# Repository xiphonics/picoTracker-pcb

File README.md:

# PCB for PicoTracker
All data in order to fabricate the PCB for the [picoTracker](https://github.com/xiphonics/picoTracker)

Buy the official kit at [xiphonics store](https://xiphonics.com/products/picotracker-pcb-kit)
# Trademark Notice

This repository contains the open-source hardware design files for the picoTracker project.

The hardware design files are released under the CC0 1.0 Universal license and may be used, modified, manufactured, and sold without restriction.

However, the **picoTracker** name, logos, product branding, and associated trademarks are **not** covered by the CC0 license and are not licensed for use by third parties.

You may manufacture and sell hardware derived from these design files, but you may not market, advertise, label, or otherwise represent such products using the "picoTracker" name or branding without prior written permission from Xiphonics.

Products manufactured from these files must be sold under a different product name and must not imply endorsement by, affiliation with, or origin from Xiphonics.

To facilitate this separation, the manufacturing files distributed through this repository intentionally omit picoTracker branding elements.

Use of the picoTracker name in connection with unauthorized derivative hardware may constitute trademark infringement and unfair competition.

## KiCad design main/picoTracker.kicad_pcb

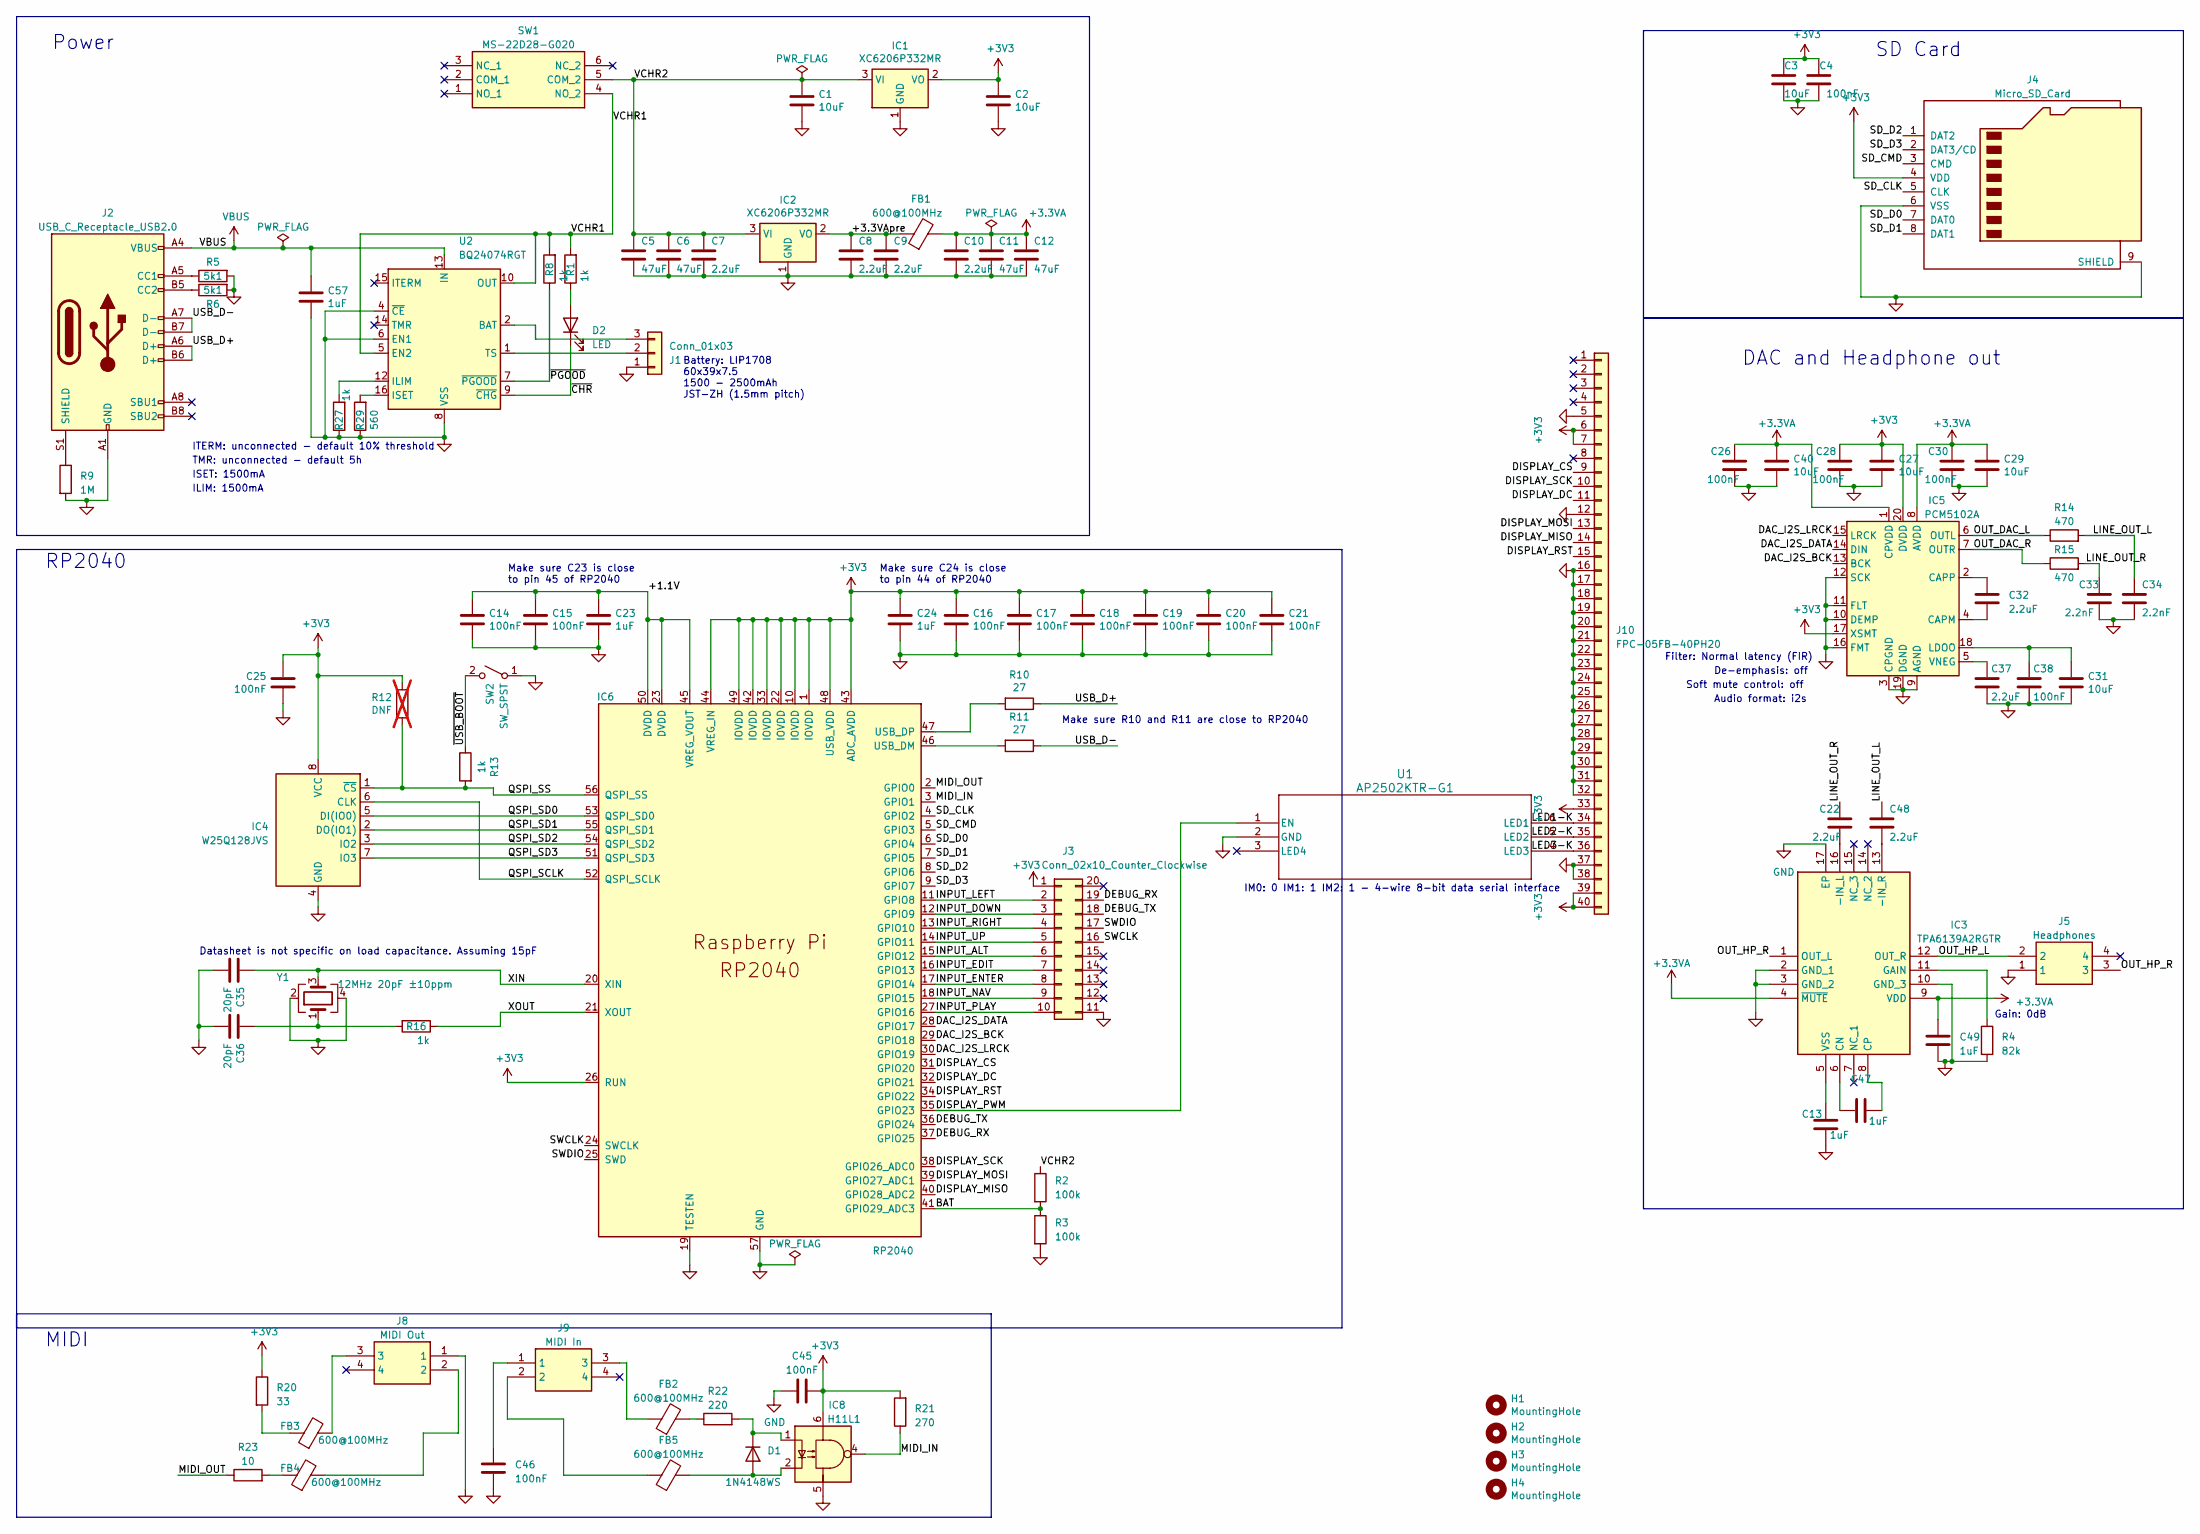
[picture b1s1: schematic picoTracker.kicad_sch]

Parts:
C1, C2, C3, C27, C29, C31, C40: 10uF; C_0603_1608Metric; LCSC C19702
C4, C14, C15, C16, C17, C18, C19, C20, C21, C25, C26, C28, C30, C38, C45, C46: 100nF; C_0603_1608Metric; LCSC C14663
C5, C6, C11, C12: 47uF; C_0805_2012Metric; LCSC C16780
C7, C8, C9, C10, C22, C32, C37, C48: 2.2uF; C_0603_1608Metric; LCSC C23630
C13, C23, C24, C47, C49, C57: 1uF; C_0603_1608Metric; LCSC C15849
C33, C34: 2.2nF; C_0603_1608Metric; LCSC C1604
C35, C36: 20pF; C_0603_1608Metric; LCSC C1648
D1: 1N4148WS; D_SOD-323; LCSC C2128
D2: LED; LED_0603_1608Metric; LCSC C2286
FB1, FB2, FB3, FB4, FB5: 600@100MHz; R_0805_2012Metric; LCSC C1017
H1, H2, H3, H4: MountingHole; MountingHole_3.2mm_M3
IC1, IC2: XC6206P332MR; SOT-23; LCSC C5446
IC3: TPA6139A2RGTR; QFN50P300X300X100-17N-D; Mouser Part Number 595-TPA6139A2RGTR
IC4: W25Q128JVS; SOIC-8_5.23x5.23mm_P1.27mm; LCSC C97521
IC5: PCM5102A; TSSOP-20_4.4x6.5mm_P0.65mm; LCSC C107671
IC6: RP2040; QFN-56-1EP_7x7mm_P0.4mm_EP3.2x3.2mm; LCSC C2040
IC8: H11L1; SMDIP-6_W9.53mm; LCSC C78589
J1: Conn_01x03; CONN_S3B-ZR-SM4A-TFLFSN_JST; LCSC C72591
J2: USB_C_Receptacle_USB2.0; USB_C_Receptacle_G-Switch_GT-USB-7010ASV; LCSC C2988369
J3: Conn_02x10_Counter_Clockwise; Hirose_DF12_DF12C3.0-20DS-0.5V_2x10_P0.50mm_Vertical; LCSC C3645324
J4: Micro_SD_Card; Xunpu_TF-115_microSD; LCSC C720505
J5: Headphones; PJ327C4A; Manufacturer_Part_Number PJ-327C-4A; LCSC C145813
J8: MIDI Out; PJ327C4A; Manufacturer_Part_Number PJ-327C-4A; LCSC C145813
J9: MIDI In; PJ327C4A; Manufacturer_Part_Number PJ-327C-4A; LCSC C145813
J10: FPC-05FB-40PH20; FPC_40-flap; LCSC C2856837
R1, R8, R13, R16, R27: 1k; R_0603_1608Metric; LCSC C21190
R2, R3: 100k; R_0603_1608Metric; LCSC C25803
R4: 82k; R_0805_2012Metric; LCSC C17840
R5, R6: 5k1; R_0603_1608Metric; LCSC C23186
R9: 1M; R_0603_1608Metric; LCSC C22935
R10, R11: 27; R_0603_1608Metric; LCSC C25190
R12: DNF; R_0603_1608Metric; not fitted
R14, R15: 470; R_0603_1608Metric; LCSC C23179
R20: 33; R_0603_1608Metric; LCSC C23140
R21: 270; R_0603_1608Metric; LCSC C22966
R22: 220; R_0402_1005Metric; LCSC C1111
R23: 10; R_0603_1608Metric; LCSC C22859
R29: 560; R_0603_1608Metric; LCSC C23204
SW1: MS-22D28-G020; MS22D28G020; Manufacturer_Part_Number MS-22D28-G020; LCSC C963205
SW2: SW_SPST; SW_Push_1P1T_XKB_TS-1187A; LCSC C318884
U1: AP2502KTR-G1; SOT23-6_DIO; LCSC C460349
U2: BQ24074RGT; VQFN-16-1EP_3x3mm_P0.5mm_EP1.6x1.6mm; LCSC C54313
Y1: 12MHz 20pF ±10ppm; Crystal_SMD_3225-4Pin_3.2x2.5mm; LCSC C9002

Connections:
+3.3VA: C10.1, C11.1, C12.1, C26.1, C29.1, C30.1, C40.1, C49.1, FB1.2, IC3.4 (~MUTE), IC3.9 (VDD), IC5.1 (CPVDD), IC5.8 (AVDD)
+3V3: C2.1, C3.1, C4.1, C16.1, C17.1, C18.1, C19.1, C20.1, C21.1, C24.1, C25.1, C27.1, C28.1, C45.2, IC1.2 (VO), IC4.8 (VCC), IC5.17 (XSMT), IC5.20 (DVDD), IC6.1 (IOVDD), IC6.10 (IOVDD), IC6.22 (IOVDD), IC6.26 (RUN), IC6.33 (IOVDD), IC6.42 (IOVDD), IC6.43 (ADC_AVDD), IC6.44 (VREG_IN), IC6.48 (USB_VDD), IC6.49 (IOVDD), IC8.6, J3.1, J4.4 (VDD), J10.6, J10.7, J10.33, J10.39, J10.40, R12.1, R20.1, R21.2
/+1.1V: C14.1, C15.1, C23.1, IC6.23 (DVDD), IC6.45 (VREG_VOUT), IC6.50 (DVDD)
/+3.3VApre: C8.1, C9.1, FB1.1, IC2.2 (VO)
/BAT: IC6.41 (GPIO29_ADC3), R2.2, R3.1
/DAC_I2S_BCK: IC5.13 (BCK), IC6.29 (GPIO18)
/DAC_I2S_DATA: IC5.14 (DIN), IC6.28 (GPIO17)
/DAC_I2S_LRCK: IC5.15 (LRCK), IC6.30 (GPIO19)
/DEBUG_RX: IC6.37 (GPIO25), J3.19
/DEBUG_TX: IC6.36 (GPIO24), J3.18
/DISPLAY_CS: IC6.31 (GPIO20), J10.9
/DISPLAY_DC: IC6.32 (GPIO21), J10.11
/DISPLAY_MISO: IC6.40 (GPIO28_ADC2), J10.14
/DISPLAY_MOSI: IC6.39 (GPIO27_ADC1), J10.13
/DISPLAY_PWM: IC6.35 (GPIO23), U1.1 (EN)
/DISPLAY_RST: IC6.34 (GPIO22), J10.15
/DISPLAY_SCK: IC6.38 (GPIO26_ADC0), J10.10
/INPUT_ALT: IC6.15 (GPIO12), J3.6
/INPUT_DOWN: IC6.12 (GPIO9), J3.3
/INPUT_EDIT: IC6.16 (GPIO13), J3.7
/INPUT_ENTER: IC6.17 (GPIO14), J3.8
/INPUT_LEFT: IC6.11 (GPIO8), J3.2
/INPUT_NAV: IC6.18 (GPIO15), J3.9
/INPUT_PLAY: IC6.27 (GPIO16), J3.10
/INPUT_RIGHT: IC6.13 (GPIO10), J3.4
/INPUT_UP: IC6.14 (GPIO11), J3.5
/LED1-K: J10.34, U1.6 (LED1)
/LED2-K: J10.35, U1.5 (LED2)
/LED3-K: J10.36, U1.4 (LED3)
/LINE_OUT_L: C34.1, C48.1, R14.2
/LINE_OUT_R: C22.1, C33.1, R15.2
/MIDI_IN: IC6.3 (GPIO1), IC8.4, R21.1
/MIDI_OUT: IC6.2 (GPIO0), R23.1
/OUT_DAC_L: IC5.6 (OUTL), R14.1
/OUT_DAC_R: IC5.7 (OUTR), R15.1
/OUT_HP_L: IC3.12 (OUT_R), J5.2
/OUT_HP_R: IC3.1 (OUT_L), J5.3
/QSPI_SCLK: IC4.6 (CLK), IC6.52 (QSPI_SCLK)
/QSPI_SD0: IC4.5 (DI(IO0)), IC6.53 (QSPI_SD0)
/QSPI_SD1: IC4.2 (DO(IO1)), IC6.55 (QSPI_SD1)
/QSPI_SD2: IC4.3 (IO2), IC6.54 (QSPI_SD2)
/QSPI_SD3: IC4.7 (IO3), IC6.51 (QSPI_SD3)
/QSPI_SS: IC4.1 (~CS), IC6.56 (QSPI_SS), R12.2, R13.2
/SD_CLK: IC6.4 (GPIO2), J4.5 (CLK)
/SD_CMD: IC6.5 (GPIO3), J4.3 (CMD)
/SD_D0: IC6.6 (GPIO4), J4.7 (DAT0)
/SD_D1: IC6.7 (GPIO5), J4.8 (DAT1)
/SD_D2: IC6.8 (GPIO6), J4.1 (DAT2)
/SD_D3: IC6.9 (GPIO7), J4.2 (DAT3/CD)
/SWCLK: IC6.24 (SWCLK), J3.16
/SWDIO: IC6.25 (SWD), J3.17
/USB_D+: J2.A6 (D+), J2.B6 (D+), R10.1
/USB_D-: J2.A7 (D-), J2.B7 (D-), R11.1
/VCHR1: R1.2, R8.2, SW1.4 (NO_2), U2.5 (EN2), U2.10 (OUT), U2.11 (OUT)
/VCHR2: C1.1, C5.1, C6.1, C7.1, IC1.3 (VI), IC2.3 (VI), R2.1, SW1.5 (COM_2)
/XIN: C35.1, IC6.20 (XIN), Y1.3
/XOUT: IC6.21 (XOUT), R16.1
/~CHR: D2.1 (K), U2.9 (~CHG)
/~PGOOD: R8.1, U2.7 (~PGOOD)
/~USB_BOOT: R13.1, SW2.2 (B)
GND: C1.2, C2.2, C3.2, C4.2, C5.2, C6.2, C7.2, C8.2, C9.2, C10.2, C11.2, C12.2, C13.2, C14.2, C15.2, C16.2, C17.2, C18.2, C19.2, C20.2, C21.2, C23.2, C24.2, C25.2, C26.2, C27.2, C28.2, C29.2, C30.2, C31.2, C33.2, C34.2, C35.2, C36.2, C37.2, C38.2, C40.2, C45.1, C46.2, C49.2, C57.2, IC1.1 (GND), IC2.1 (GND), IC3.2 (GND_1), IC3.3 (GND_2), IC3.10 (GND_3), IC3.17 (EP), IC4.4 (GND), IC5.3 (CPGND), IC5.9 (AGND), IC5.10 (DEMP), IC5.11 (FLT), IC5.12 (SCK), IC5.16 (FMT), IC5.19 (DGND), IC6.19 (TESTEN), IC6.57 (GND), IC8.5, J1.1, J2.A1 (GND), J2.A12 (GND), J2.B1 (GND), J2.B12 (GND), J3.11, J4.6 (VSS), J4.9 (SHIELD), J5.1, J8.1, J10.5, J10.12, J10.16, J10.17, J10.18, J10.19, J10.20, J10.21, J10.22, J10.23, J10.24, J10.25, J10.26, J10.27, J10.28, J10.29, J10.30, J10.31, J10.32, J10.37, J10.38, R3.2, R4.2, R5.2, R6.2, R9.2, R27.1, R29.1, SW2.1 (A), U1.2 (GND), U2.4 (~CE), U2.6 (EN1), U2.8 (VSS), U2.17 (VSS), Y1.2, Y1.4
unnamed: C36.1, R16.2, Y1.1
unnamed: C46.1, J9.1
unnamed: D1.2 (A), FB5.2, IC8.2
unnamed: D1.1 (K), IC8.1, R22.2
unnamed: D2.2 (A), R1.1
unnamed: FB2.1, J9.3
unnamed: FB2.2, R22.1
unnamed: FB3.1, R20.2
unnamed: FB3.2, J8.3
unnamed: FB4.1, R23.2
unnamed: FB4.2, J8.2
unnamed: FB5.1, J9.2
unnamed: C22.2, IC3.16 (-IN_L)
unnamed: C48.2, IC3.13 (-IN_R)
unnamed: C47.1, IC3.6 (CN)
unnamed: C47.2, IC3.8 (CP)
unnamed: IC3.11 (GAIN), R4.1
unnamed: C13.1, IC3.5 (VSS)
unnamed: C32.2, IC5.4 (CAPM)
unnamed: C32.1, IC5.2 (CAPP)
unnamed: C31.1, C38.1, IC5.18 (LDOO)
unnamed: C37.1, IC5.5 (VNEG)
unnamed: IC6.46 (USB_DM), R11.2
unnamed: IC6.47 (USB_DP), R10.2
unnamed: J1.2, U2.1 (TS)
unnamed: J1.3, U2.2 (BAT), U2.3 (BAT)
unnamed: J2.A5 (CC1), R5.1
unnamed: J2.B5 (CC2), R6.1
unnamed: J2.S1 (SHIELD), R9.1
unnamed: R27.2, U2.12 (ILIM)
unnamed: R29.2, U2.16 (ISET)
VBUS: C57.1, J2.A4 (VBUS), J2.A9 (VBUS), J2.B4 (VBUS), J2.B9 (VBUS), U2.13 (IN)

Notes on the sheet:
DAC and Headphone out
Gain: 0dB
ITERM: unconnected - default 10% threshold
SD Card
Battery: LIP1708 60x39x7.5 1500 - 2500mAh JST-ZH (1.5mm pitch)
Power
RP2040
Filter: Normal latency (FIR)
IM0: 0 IM1: 1 IM2: 1 - 4-wire 8-bit data serial interface
Datasheet is not specific on load capacitance. Assuming 15pF
ILIM: 1500mA
ISET: 1500mA
TMR: unconnected - default 5h
Make sure C23 is close to pin 45 of RP2040
Soft mute control: off
Make sure R10 and R11 are close to RP2040
De-emphasis: off
MIDI
Audio format: i2s
Make sure C24 is close to pin 44 of RP2040

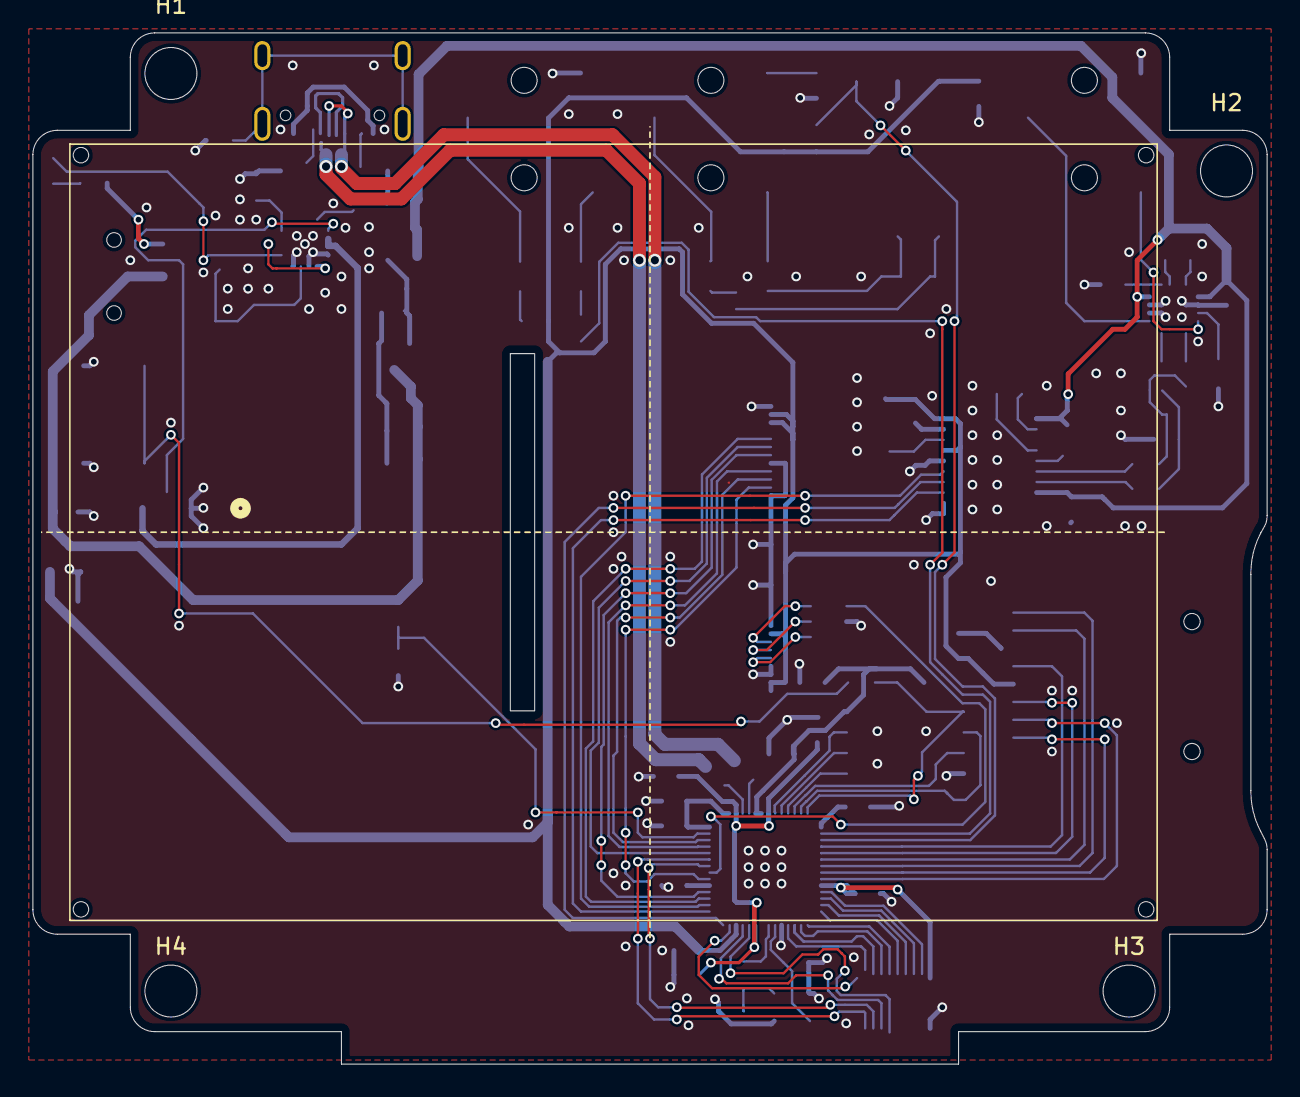
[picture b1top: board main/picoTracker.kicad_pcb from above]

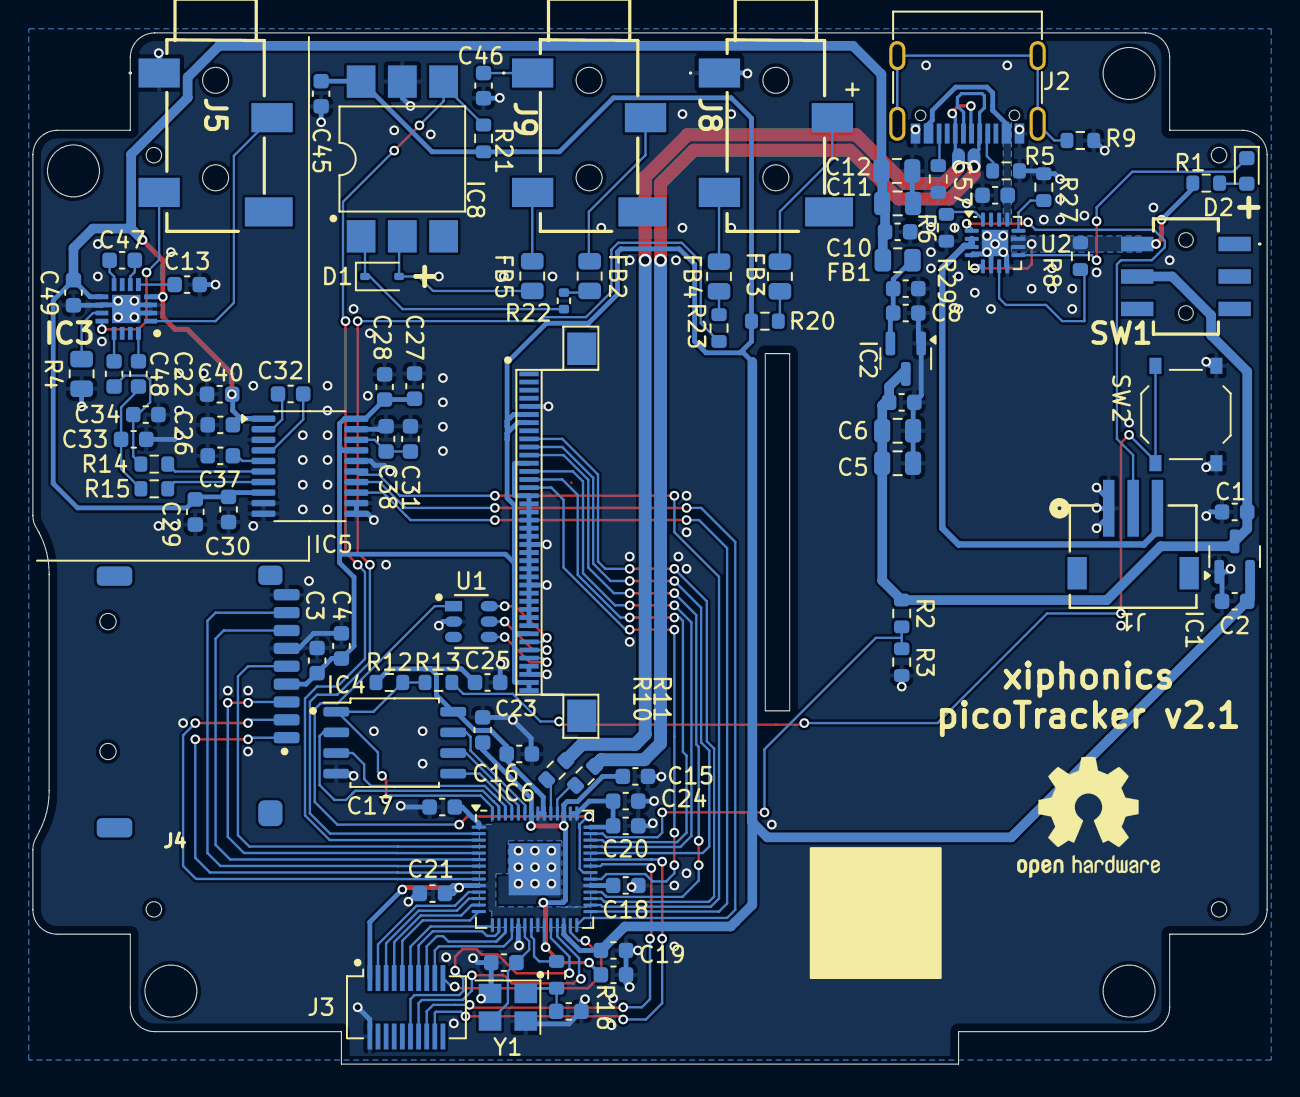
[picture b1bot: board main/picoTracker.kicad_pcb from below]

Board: 2 copper layers, 76.0 x 63.5 mm, 97 parts (93 on the bottom side), 93 nets.

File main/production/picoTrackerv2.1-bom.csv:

Designator,Footprint,Quantity,Value,LCSC Part #
"C1, C2, C27, C29, C3, C31, C40",0603,7,10uF,C19702
"C10, C22, C32, C37, C48, C7, C8, C9",0603,8,2.2uF,C23630
"C11, C12, C5, C6",0805,4,47uF,C16780
"C13, C23, C24, C47, C49, C57",0603,6,1uF,C15849
"C14, C15, C16, C17, C18, C19, C20, C21, C25, C26, C28, C30, C38, C4, C45, C46",0603,16,100nF,C14663
"C33, C34",0603,2,2.2nF,C1604
"C35, C36",0603,2,20pF,C1648
D1,D_SOD-323,1,1N4148WS,C2128
D2,0603,1,LED,C2286
"FB1, FB2, FB3, FB4, FB5",0805,5,600@100MHz,C1017
"H1, H2, H3, H4",MountingHole_3.2mm_M3,4,MountingHole,
"IC1, IC2",SOT-23,2,XC6206P332MR,C5446
IC3,QFN50P300X300X100-17N-D,1,TPA6139A2RGTR,C2868391
IC4,SOIC-8_5.23x5.23mm_P1.27mm,1,W25Q128JVS,C97521
IC5,TSSOP-20_4.4x6.5mm_P0.65mm,1,PCM5102A,C107671
IC6,QFN-56-1EP_7x7mm_P0.4mm_EP3.2x3.2mm,1,RP2040,C2040
IC8,SMDIP-6_W9.53mm,1,H11L1,C78589
J1,CONN_S3B-ZR-SM4A-TFLFSN_JST,1,Conn_01x03,C72591
J10,FPC_40-flap,1,FPC-05FB-40PH20,C2856837
J2,USB_C_Receptacle_G-Switch_GT-USB-7010ASV,1,USB_C_Receptacle_USB2.0,C2988369
J3,Hirose_DF12_DF12C3.0-20DS-0.5V_2x10_P0.50mm_Vertical,1,Conn_02x10_Counter_Clockwise,C3645324
J4,Xunpu_TF-115_microSD,1,Micro_SD_Card,C720505
J5,PJ327C4A,1,Headphones,C145813
J8,PJ327C4A,1,MIDI Out,C145813
J9,PJ327C4A,1,MIDI In,C145813
"R1, R13, R16, R27, R8",0603,5,1k,C21190
"R10, R11",0603,2,27,C25190
R12,0603,1,DNF,
"R14, R15",0603,2,470,C23179
"R2, R3",0603,2,100k,C25803
R20,0603,1,33,C23140
R21,0603,1,270,C22966
R22,0402,1,220,C1111
R23,0603,1,10,C22859
R29,0603,1,560,C23204
R4,0805,1,82k,C17840
"R5, R6",0603,2,5k1,C23186
R9,0603,1,1M,C22935
SW1,MS22D28G020,1,MS-22D28-G020,C963205
SW2,SW_Push_1P1T_XKB_TS-1187A,1,SW_SPST,C318884
U1,SOT23-6_DIO,1,AP2502KTR-G1,C460349
U2,VQFN-16-1EP_3x3mm_P0.5mm_EP1.6x1.6mm,1,BQ24074RGT,C54313
Y1,Crystal_SMD_3225-4Pin_3.2x2.5mm,1,12MHz 20pF ±10ppm,C9002

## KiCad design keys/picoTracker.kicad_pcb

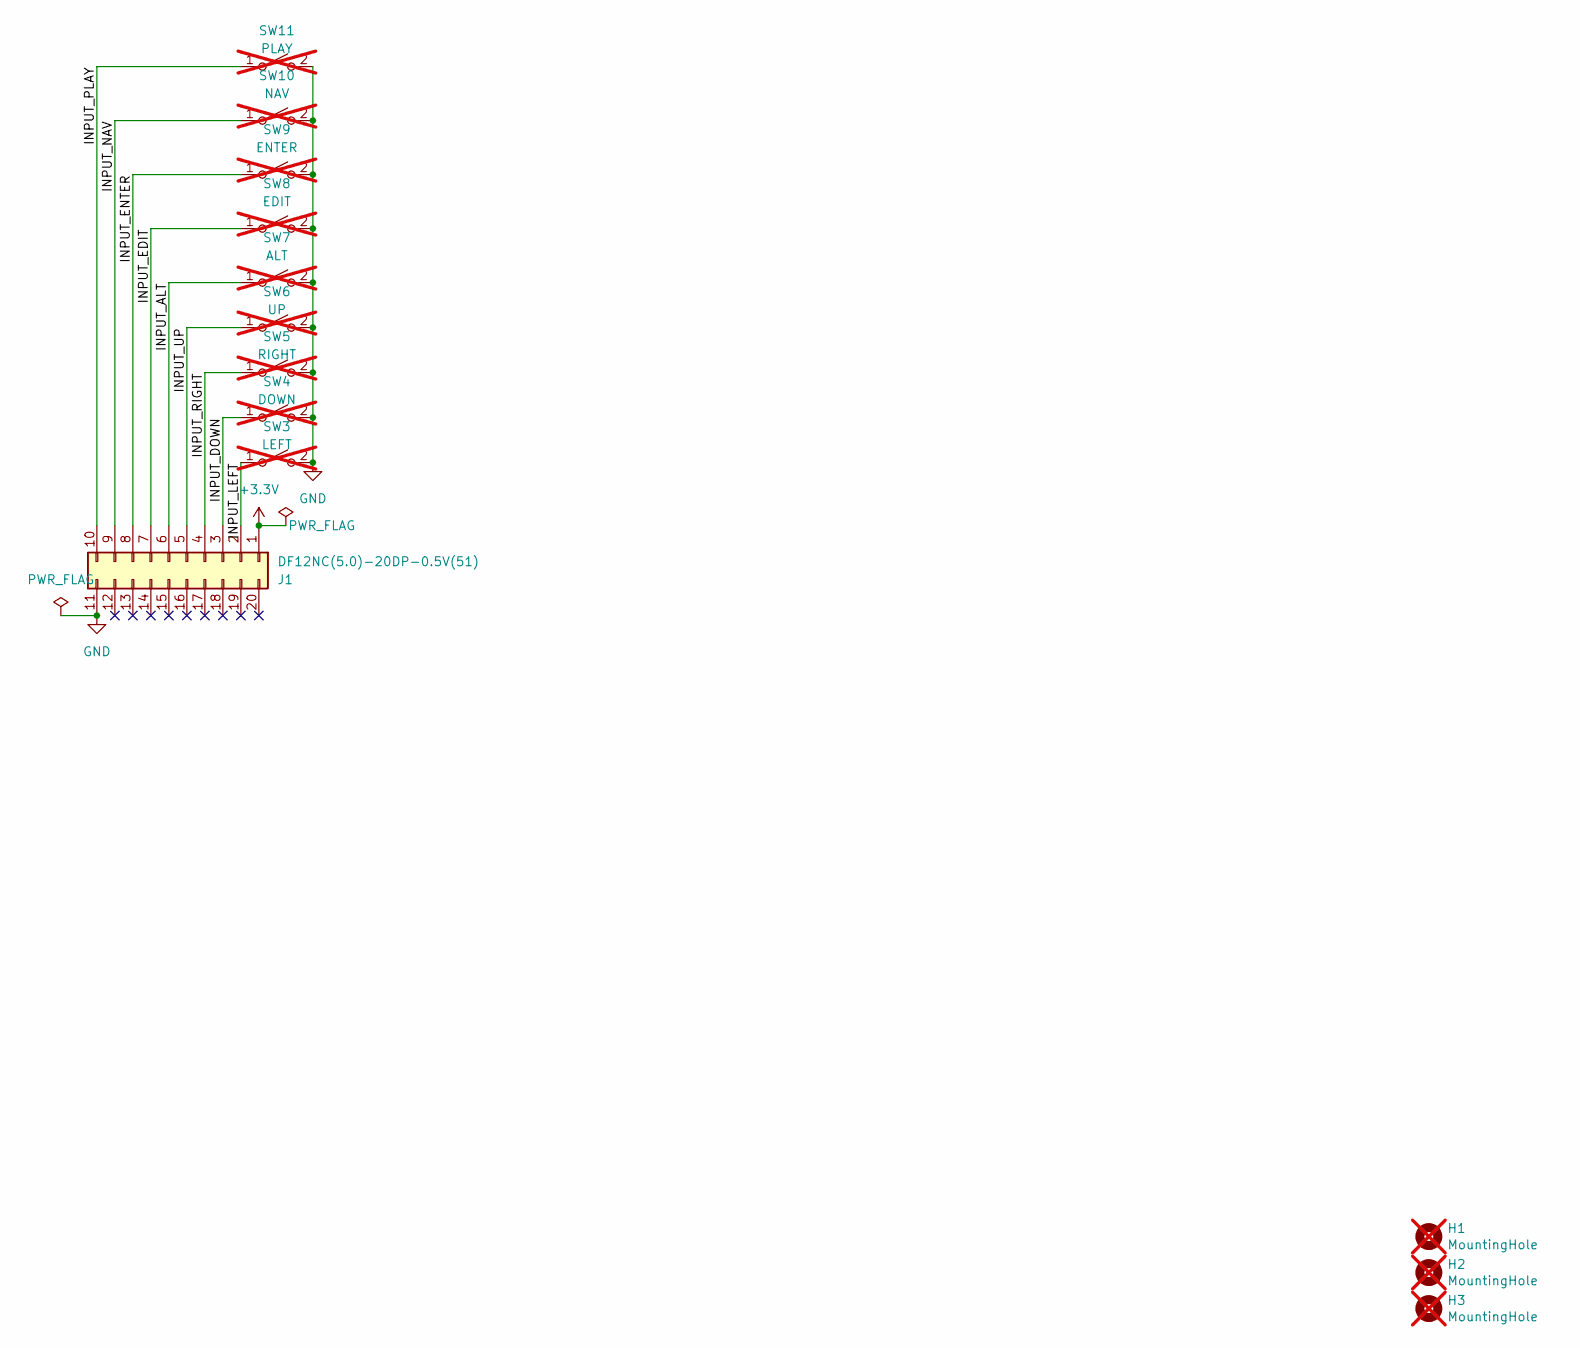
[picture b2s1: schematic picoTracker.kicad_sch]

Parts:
H1, H2, H3: MountingHole; MountingHole_3.2mm_M3; not fitted
J1: DF12NC(5.0)-20DP-0.5V(51); Hirose_DF12_DF12E3.0-20DP-0.5V_2x10_P0.50mm_Vertical; LCSC C3650665
SW3: LEFT; Cherry-MX-Low-Profile-kailh; LCSC C400229; not fitted
SW4: DOWN; Cherry-MX-Low-Profile-kailh; LCSC C400229; not fitted
SW5: RIGHT; Cherry-MX-Low-Profile-kailh; LCSC C400229; not fitted
SW6: UP; Cherry-MX-Low-Profile-kailh; LCSC C400229; not fitted
SW7: ALT; Cherry-MX-Low-Profile-kailh; LCSC C400229; not fitted
SW8: EDIT; Cherry-MX-Low-Profile-kailh; LCSC C400229; not fitted
SW9: ENTER; Cherry-MX-Low-Profile-kailh; LCSC C400229; not fitted
SW10: NAV; Cherry-MX-Low-Profile-kailh; LCSC C400229; not fitted
SW11: PLAY; Cherry-MX-Low-Profile-kailh; LCSC C400229; not fitted

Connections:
+3.3V: J1.1
/INPUT_ALT: J1.6, SW7.1 (A)
/INPUT_DOWN: J1.3, SW4.1 (A)
/INPUT_EDIT: J1.7, SW8.1 (A)
/INPUT_ENTER: J1.8, SW9.1 (A)
/INPUT_LEFT: J1.2, SW3.1 (A)
/INPUT_NAV: J1.9, SW10.1 (A)
/INPUT_PLAY: J1.10, SW11.1 (A)
/INPUT_RIGHT: J1.4, SW5.1 (A)
/INPUT_UP: J1.5, SW6.1 (A)
GND: J1.11, SW3.2 (B), SW4.2 (B), SW5.2 (B), SW6.2 (B), SW7.2 (B), SW8.2 (B), SW9.2 (B), SW10.2 (B), SW11.2 (B)

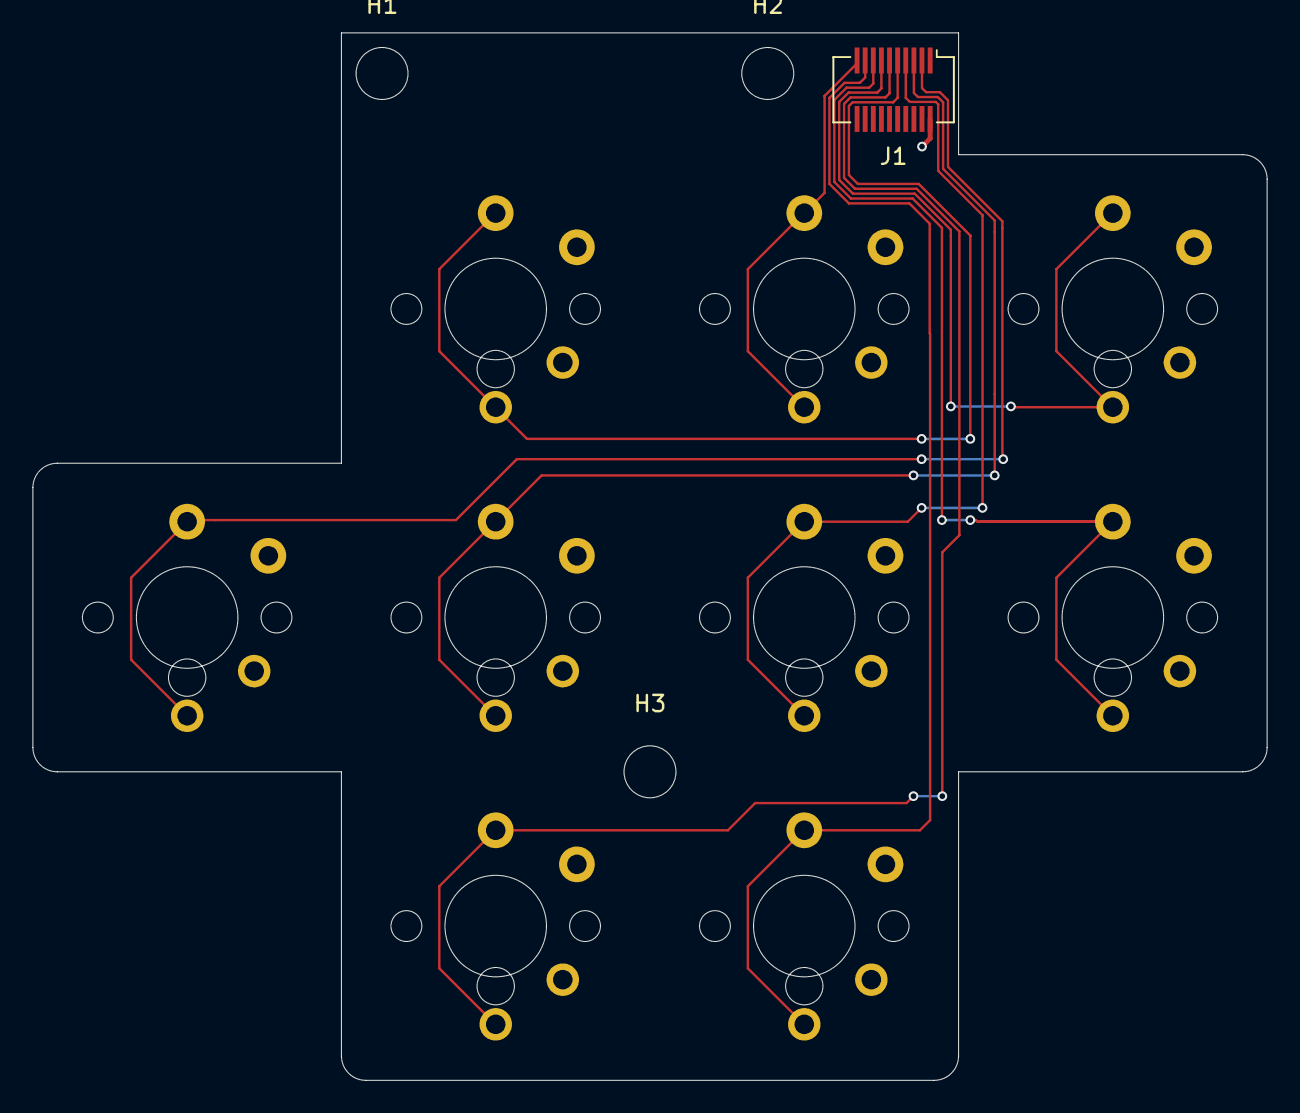
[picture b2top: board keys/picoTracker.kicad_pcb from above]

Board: 2 copper layers, 76.0 x 64.5 mm, 13 parts (0 on the bottom side), 10 nets.

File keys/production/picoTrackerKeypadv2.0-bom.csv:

Designator,Footprint,Quantity,Value,LCSC Part #
"H1, H2, H3",MountingHole_3.2mm_M3,3,MountingHole,
J1,Hirose_DF12_DF12E3.0-20DP-0.5V_2x10_P0.50mm_Vertical,1,DF12NC(5.0)-20DP-0.5V(51),C3650665
SW10,Cherry-MX-Low-Profile-kailh,1,NAV,C400229
SW11,Cherry-MX-Low-Profile-kailh,1,PLAY,C400229
SW3,Cherry-MX-Low-Profile-kailh,1,LEFT,C400229
SW4,Cherry-MX-Low-Profile-kailh,1,DOWN,C400229
SW5,Cherry-MX-Low-Profile-kailh,1,RIGHT,C400229
SW6,Cherry-MX-Low-Profile-kailh,1,UP,C400229
SW7,Cherry-MX-Low-Profile-kailh,1,ALT,C400229
SW8,Cherry-MX-Low-Profile-kailh,1,EDIT,C400229
SW9,Cherry-MX-Low-Profile-kailh,1,ENTER,C400229

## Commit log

2025-03-28 picoTracker PCB v2.1 and picoTrackerKeypad PCB v2.0
2025-03-28 updated pcb render
2025-03-28 Added bezel v2.0
2026-05-29 Update README with trademark and licensing details
    Added trademark notice and licensing information for picoTracker.
2026-05-29 Add purchase link for PicoTracker kit in README
